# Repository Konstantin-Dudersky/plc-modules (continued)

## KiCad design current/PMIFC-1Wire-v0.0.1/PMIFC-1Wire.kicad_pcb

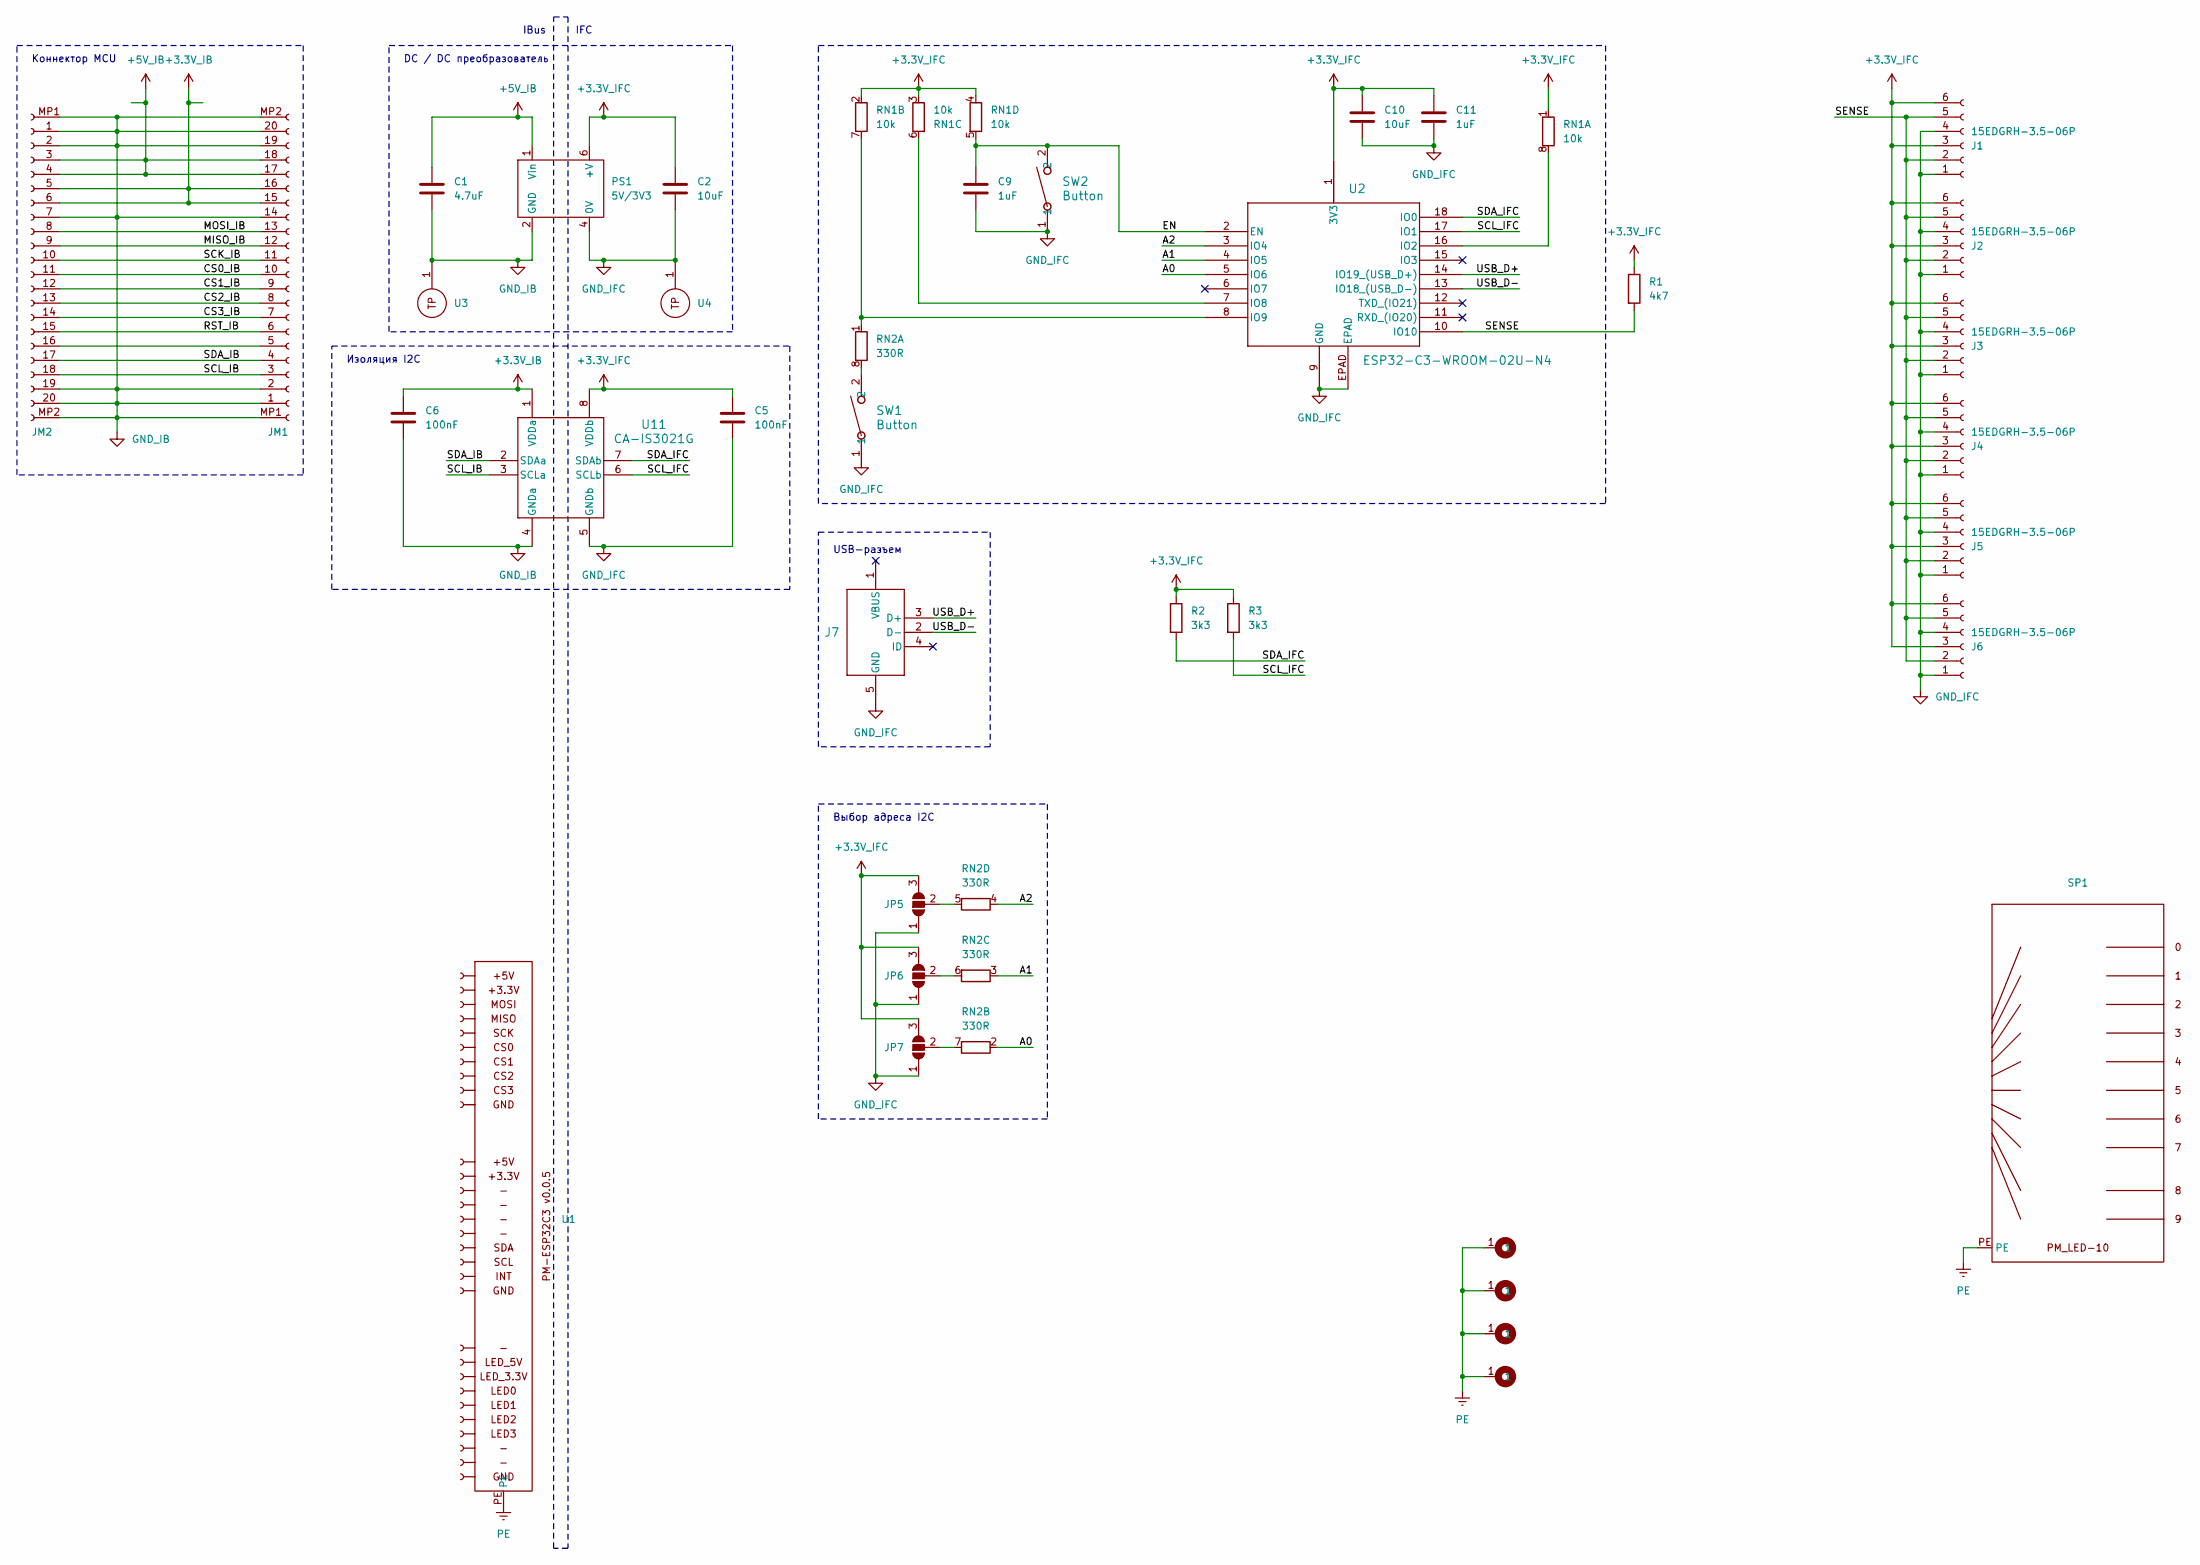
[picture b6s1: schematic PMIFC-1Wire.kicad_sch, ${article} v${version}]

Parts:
C1: 4.7uF; C_0805_2012Metric; part_ipn C_4.7uF_16V_0805_MLCC-X7R
C2, C10: 10uF; C_0805_2012Metric; part_ipn C_10uF_16V_0805_MLCC-X7R
C5, C6: 100nF; C_0603_1608Metric; part_ipn C_100nF_16V_0603_MLCC-X7R
C9, C11: 1uF; C_0603_1608Metric; part_ipn C_1uF_16V_0603_MLCC-X7R
H1, H2, H3, H4: M4; MountingHole_4.3mm_M4_Pad_Via
J1, J2, J3, J4, J5, J6: 15EDGRH-3.5-06P; part_ipn 15EDGRH-3.5-06P
J7: U254-051T-4BH83-S1S; CONN5_H83-S1S_XKB; part_ipn U254-051T-4BH83-S1S
JM1, JM2: AFA07-S20FCC-00; AFA07S20FCA00; part_ipn AFA07-S20FCC-00
JP5, JP6, JP7: SolderJumper_3_Open; SolderJumper-3_P1.3mm_Open_Pad1.0x1.5mm
PS1: 5V/3V3; B2405LS-1WR3; part_ipn B0503S-2W
R1: 4k7; R_0603_1608Metric; part_ipn R_4k7_0603_1%
R2, R3: 3k3; R_0603_1608Metric; part_ipn R_3k3_0603_1%
RN1: 10k; R_Array_Convex_4x0603; part_ipn R_10k_0603x4_1%
RN2: 330R; R_Array_Convex_4x0603; part_ipn R_330R_0603x4_1%
SP1: PMLED-xx-v0.0.2; part_ipn PMLED-10-v0.0.2
SW1, SW2: Button; SW_TS-1088_XNP-M; part_ipn TS-1088-AR02016
U1: PM-ESP32C3_v0.0.7; part_ipn PM_MCU-ESP32_C3-v0.0.7
U2: ESP32-C3-WROOM-02U-N4; ESP32-C3-WROOM-02U_EXP; part_ipn ESP32-C3-WROOM-02U-N4
U3, U4: 5117; part_ipn Keystone_5117
U11: CA-IS3021G; SOICW8_CLG; part_ipn CA-IS3021G

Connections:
+3.3V_IB: C6.1, JM1.15 (Pin_11), JM1.16 (Pin_11), JM2.5, JM2.6, U11.1 (VDDa)
+3.3V_IFC: C2.1, C5.1, C10.1, C11.1, J1.3, J1.6, J2.3, J2.6, J3.3, J3.6, J4.3, J4.6, J5.3, J5.6, J6.3, J6.6, JP5.3 (B), JP6.3 (B), JP7.3 (B), PS1.6 (+V), R1.1, R2.1, R3.1, RN1.1 (R1.1), RN1.2 (R2.1), RN1.3 (R3.1), RN1.4 (R4.1), U2.1 (3V3), U11.8 (VDDb)
+5V_IB: C1.1, JM1.17 (Pin_11), JM1.18 (Pin_11), JM2.3, JM2.4, PS1.1 (Vin)
/A0: RN2.2 (R2.1), U2.5 (IO6)
/A1: RN2.3 (R3.1), U2.4 (IO5)
/A2: RN2.4 (R4.1), U2.3 (IO4)
/CS0_IB: JM1.10, JM2.11
/CS1_IB: JM1.9, JM2.12 (Pin_11)
/CS2_IB: JM1.8, JM2.13 (Pin_11)
/CS3_IB: JM1.7, JM2.14 (Pin_11)
/EN: C9.1, RN1.5 (R4.2), SW2.2, U2.2 (EN)
/MISO_IB: JM1.12 (Pin_11), JM2.9
/MOSI_IB: JM1.13 (Pin_11), JM2.8
/RST_IB: JM1.6, JM2.15 (Pin_11)
/SCK_IB: JM1.11, JM2.10
/SCL_IB: JM1.3, JM2.18 (Pin_11), U11.3 (SCLa)
/SCL_IFC: R3.2, U2.17 (IO1), U11.6 (SCLb)
/SDA_IB: JM1.4, JM2.17 (Pin_11), U11.2 (SDAa)
/SDA_IFC: R2.2, U2.18 (IO0), U11.7 (SDAb)
/SENSE: J1.2, J1.5, J2.2, J2.5, J3.2, J3.5, J4.2, J4.5, J5.2, J5.5, J6.2, J6.5, R1.2, U2.10 (IO10)
/USB_D+: J7.3 (D+), U2.14 (IO19_(USB_D+))
/USB_D-: J7.2 (D-), U2.13 (IO18_(USB_D-))
GND_IB: C1.2, C6.2, JM1.1, JM1.2, JM1.14 (Pin_11), JM1.19 (Pin_11), JM1.20 (Pin_11), JM1.MP1 (Pin_11), JM1.MP2 (Pin_11), JM2.1, JM2.2, JM2.7, JM2.19 (Pin_11), JM2.20 (Pin_11), JM2.MP1 (Pin_11), JM2.MP2 (Pin_11), PS1.2 (GND), U3.1, U11.4 (GNDa)
GND_IFC: C2.2, C5.2, C9.2, C10.2, C11.2, J1.1, J1.4, J2.1, J2.4, J3.1, J3.4, J4.1, J4.4, J5.1, J5.4, J6.1, J6.4, J7.5 (GND), JP5.1 (A), JP6.1 (A), JP7.1 (A), PS1.4 (0V), SW1.1, SW2.1, U2.9 (GND), U2.EPAD, U4.1, U11.5 (GNDb)
unnamed: JM1.5, JM2.16 (Pin_11)
unnamed: JP5.2 (C), RN2.5 (R4.2)
unnamed: JP6.2 (C), RN2.6 (R3.2)
unnamed: JP7.2 (C), RN2.7 (R2.2)
unnamed: RN1.8 (R1.2), U2.16 (IO2)
unnamed: RN1.7 (R2.2), RN2.1 (R1.1), U2.8 (IO9)
unnamed: RN1.6 (R3.2), U2.7 (IO8)
unnamed: RN2.8 (R1.2), SW1.2
PE: H1.1, H2.1, H3.1, H4.1, SP1.PE, U1.PE

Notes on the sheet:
DC / DC преобразователь
IBus
Изоляция I2C
Выбор адреса I2C
USB-разъем
IFC
Коннектор MCU

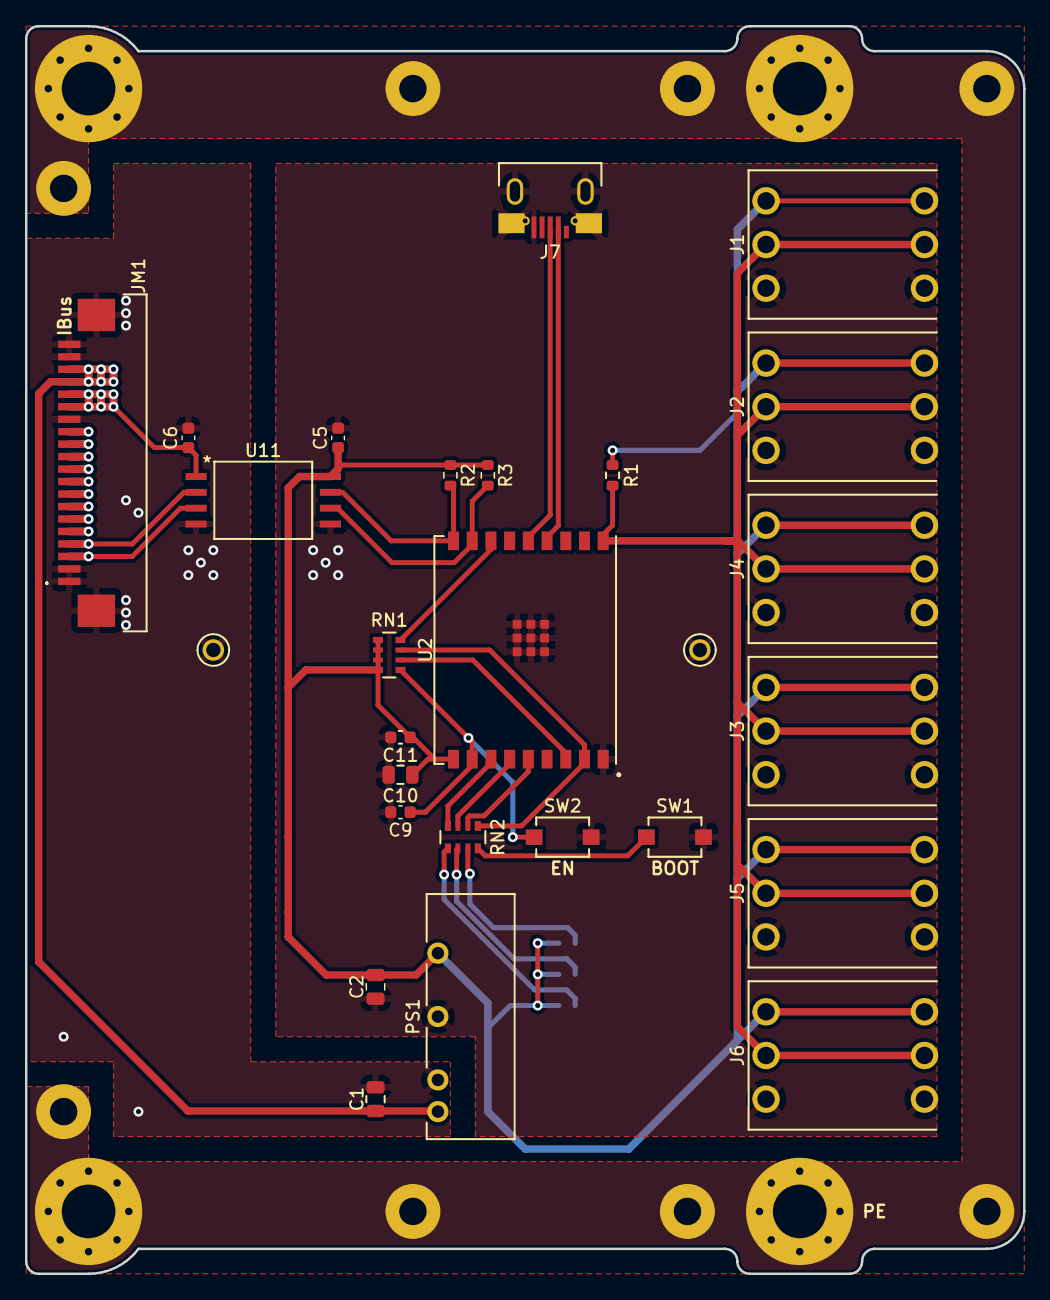
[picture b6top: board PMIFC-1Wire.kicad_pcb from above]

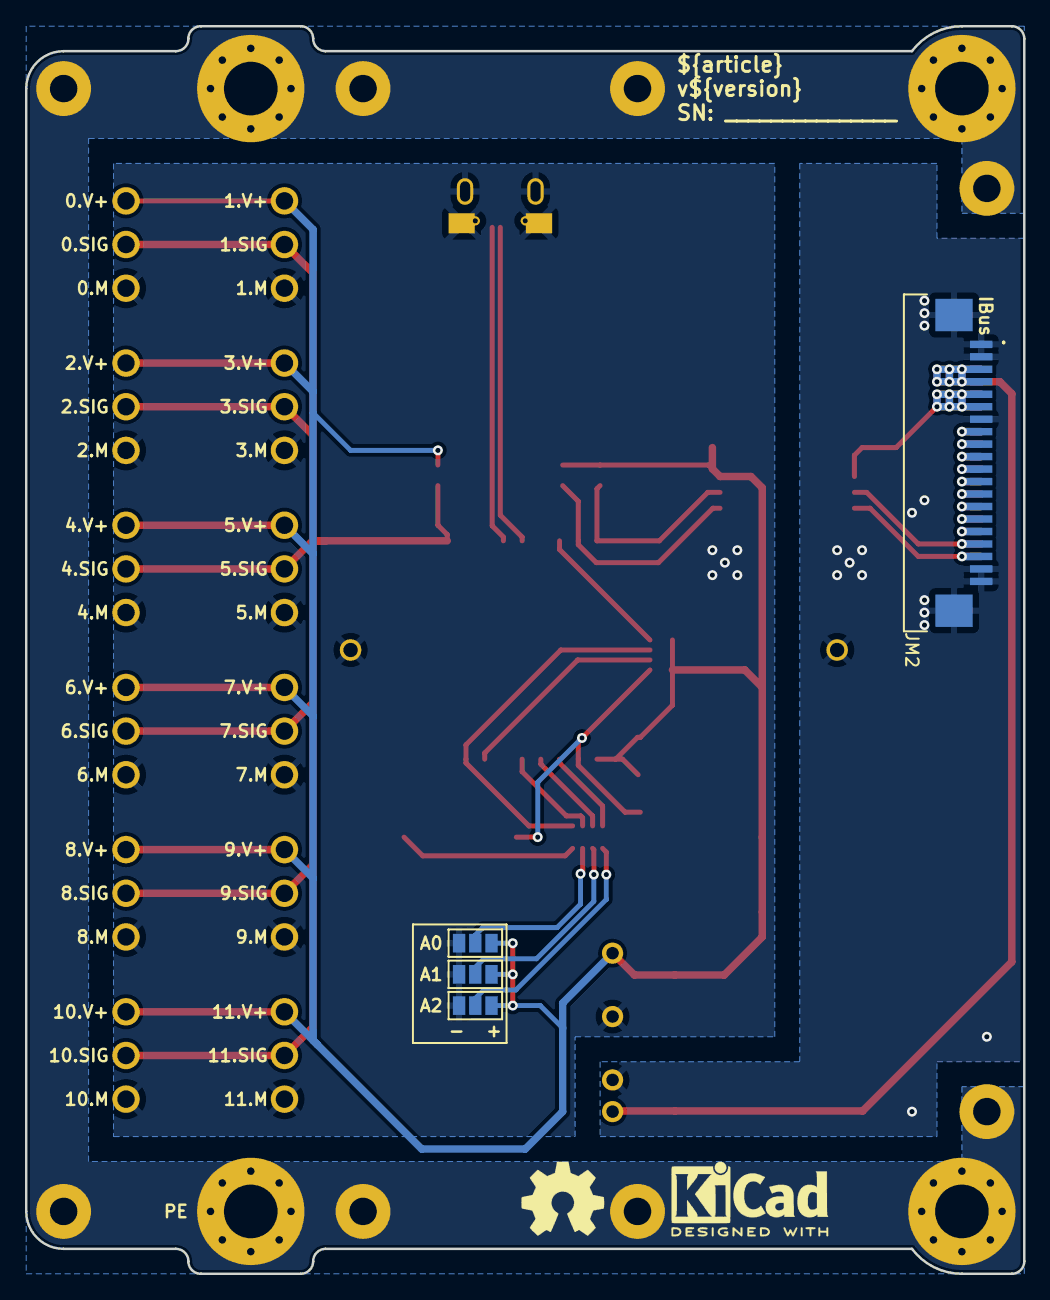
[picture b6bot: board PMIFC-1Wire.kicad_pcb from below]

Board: 2 copper layers, 80.0 x 100.0 mm, 39 parts (6 on the bottom side), 33 nets.

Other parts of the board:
kicad_logo: KiCad-Logo2_5mm_SilkScreen
oshw_logo: OSHW-Symbol_6.7x6mm_SilkScreen
